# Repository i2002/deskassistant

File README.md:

# Deskassistant

## Introduction
Deskassistant is a compact device designed to help you increase your productivity. Placed on your desk, it keeps track of your priorities for the day and the time spent for each one. This project was presented as my graduation thesis for Computer Engineering Bachelor's Degree at Faculty of Mathematics and Computer Science, University of Bucharest.

## Repository structure
This repository contains the following:
- the software application written in QT
- PCB design for the connection board between Raspberry Pi Compute Module 5 and the rest of the peripherals (LCD display, touchscreen input, side buttons, brightness control, USB 2.0 interface)
- 3D design for the case backplate
- information about the OS-level configuration

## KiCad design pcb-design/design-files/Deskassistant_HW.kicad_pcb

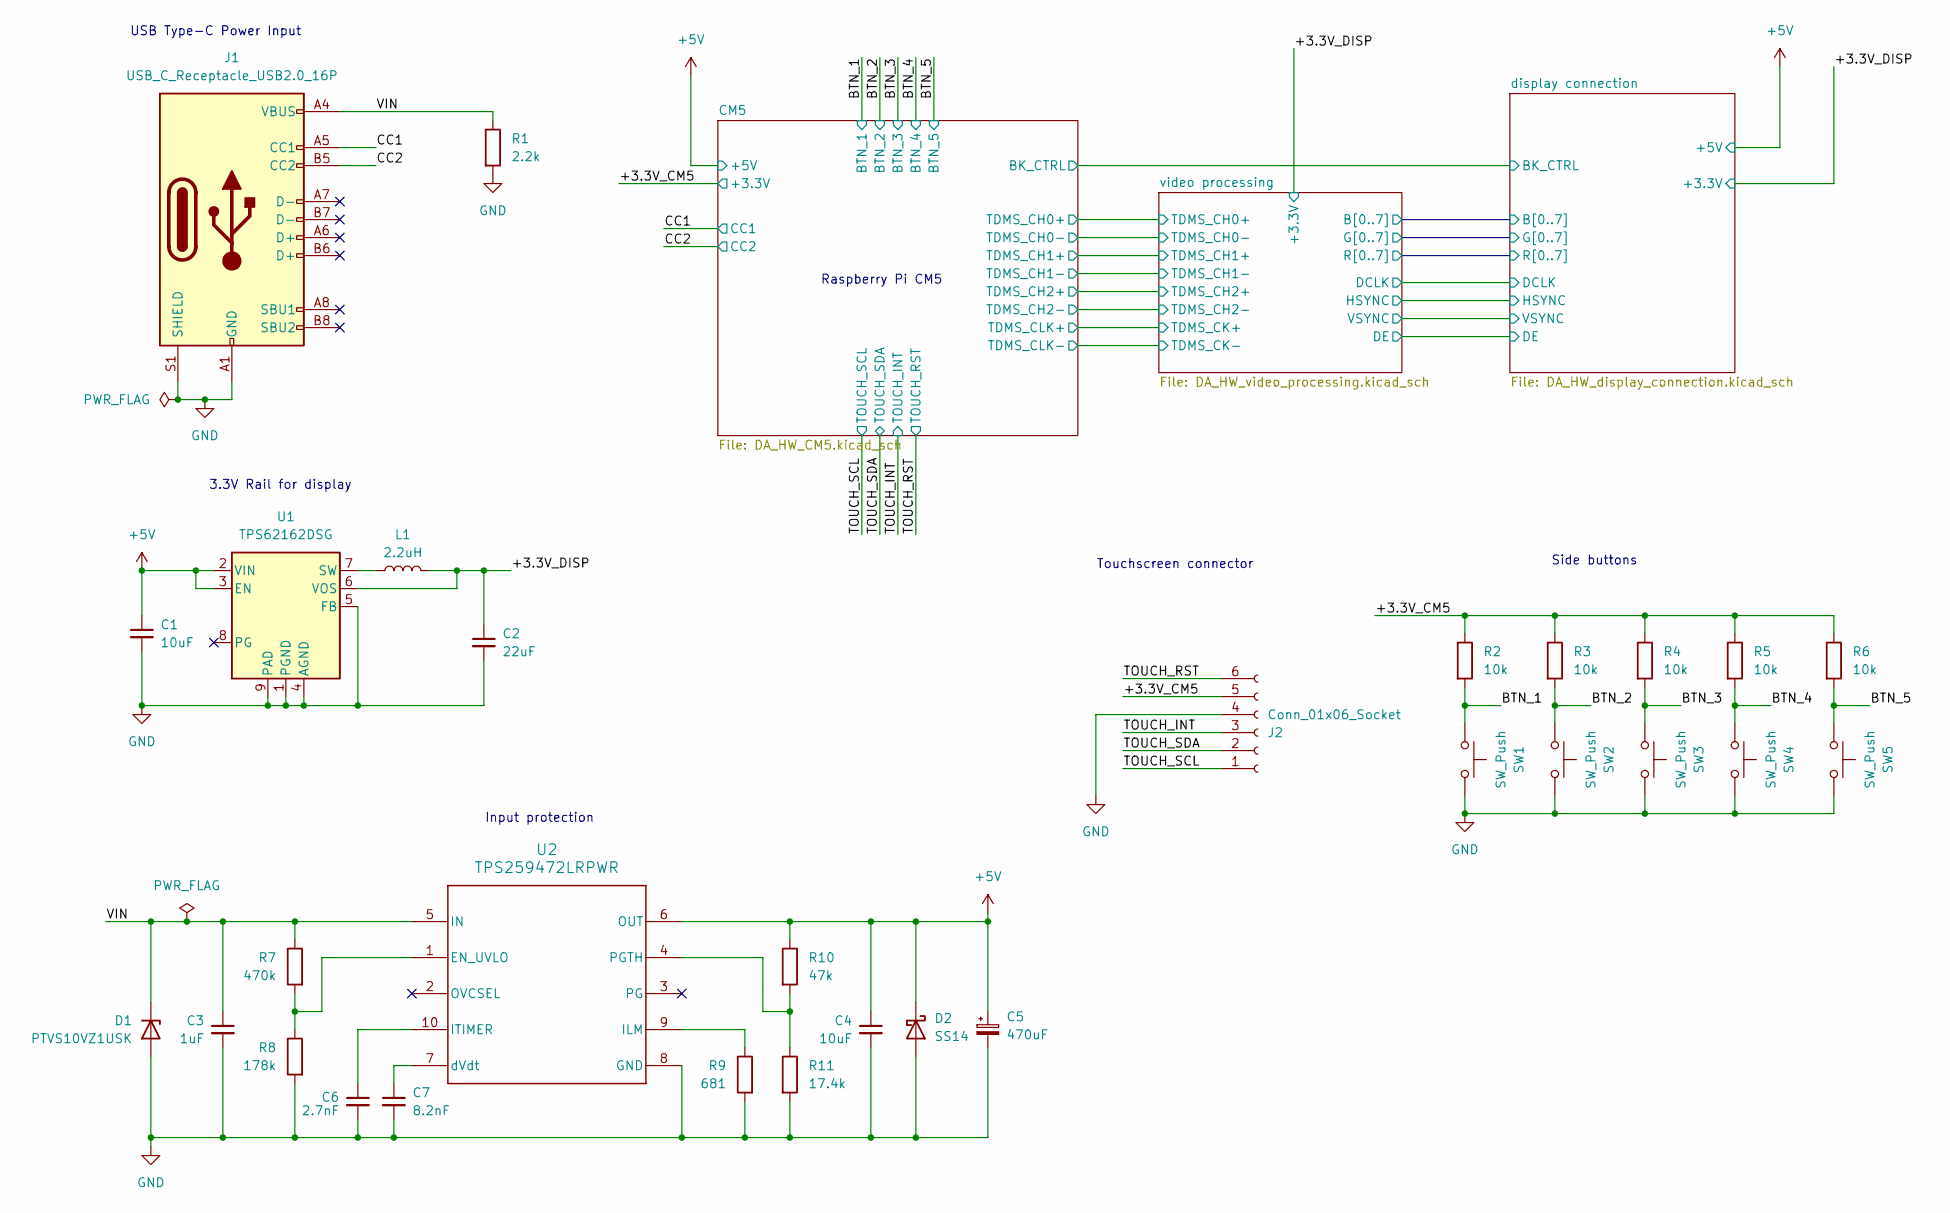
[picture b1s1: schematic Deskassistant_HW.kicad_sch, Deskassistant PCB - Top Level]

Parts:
C1, C4: 10uF; C_0805_2012Metric
C2: 22uF; C_0805_2012Metric
C3: 1uF; C_0805_2012Metric
C5: 470uF; CAPAE1030X1050L350X90N
C6: 2.7nF; C_0805_2012Metric
C7: 8.2nF; C_0805_2012Metric
D1: PTVS10VZ1USK; DIONM510X266X229L115X145N
D2: SS14; D_SMA
J1: USB_C_Receptacle_USB2.0_16P; CONN_GCT_USB4145-03-0170-C
J2: Conn_01x06_Socket; MOLEX_0527460671
L1: 2.2uH; L_NR3015T2R2M
R1: 2.2k; R_0805_2012Metric
R2, R3, R4, R5, R6: 10k; R_0805_2012Metric
R7: 470k; R_0805_2012Metric
R8: 178k; R_0805_2012Metric
R9: 681; R_0805_2012Metric
R10: 47k; R_0805_2012Metric
R11: 17.4k; R_0805_2012Metric
SW1, SW2, SW3, SW4, SW5: SW_Push; SW_ESWITCH_TL3330AF260QG
U1: TPS62162DSG; SON50P200X200X80-9N
U2: TPS259472LRPWR; ICS_TI_TPS259472ARPWR

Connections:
+5V: C1.1, C4.1, C5.1, D2.1 (K), R10.1, U1.2 (VIN), U1.3 (EN), U2.6 (OUT); also elsewhere on the board
/+3.3V_CM5: J2.5, R2.1, R3.1, R4.1, R5.1, R6.1; also elsewhere on the board
/+3.3V_DISP: C2.1, L1.2, U1.6 (VOS); also elsewhere on the board
/BTN_1: R2.2, SW1.1; also elsewhere on the board
/BTN_2: R3.2, SW2.1; also elsewhere on the board
/BTN_3: R4.2, SW3.1; also elsewhere on the board
/BTN_4: R5.2, SW4.1; also elsewhere on the board
/BTN_5: R6.2, SW5.1; also elsewhere on the board
/CC1: J1.A5 (CC1); also elsewhere on the board
/CC2: J1.B5 (CC2); also elsewhere on the board
/TOUCH_INT: J2.3; also elsewhere on the board
/TOUCH_RST: J2.6; also elsewhere on the board
/TOUCH_SCL: J2.1; also elsewhere on the board
/TOUCH_SDA: J2.2; also elsewhere on the board
/VIN: C3.1, D1.1 (K), J1.A4 (VBUS), J1.A9 (VBUS), J1.B4 (VBUS), J1.B9 (VBUS), R1.1, R7.1, U2.5 (IN)
GND: C1.2, C2.2, C3.2, C4.2, C5.2, C6.2, C7.2, D1.2 (A), D2.2 (A), J1.A1 (GND), J1.A12 (GND), J1.B1 (GND), J1.B12 (GND), J1.S1 (SHIELD), J2.4, J2.7, R1.2, R8.2, R9.2, R11.2, SW1.2, SW2.2, SW3.2, SW4.2, SW5.2, U1.1 (PGND), U1.4 (AGND), U1.5 (FB), U1.9 (PAD), U1.10, U1.11, U2.8 (GND); also elsewhere on the board
unnamed: L1.1, U1.7 (SW)
unnamed: R7.2, R8.1, U2.1 (EN_UVLO)
unnamed: R9.1, U2.9 (ILM)
unnamed: C6.1, U2.10 (ITIMER)
unnamed: R10.2, R11.1, U2.4 (PGTH)
unnamed: C7.1, U2.7 (dVdt)

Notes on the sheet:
3.3V Rail for display
USB Type-C Power Input
Input protection
Touchscreen connector
Side buttons
Raspberry Pi CM5

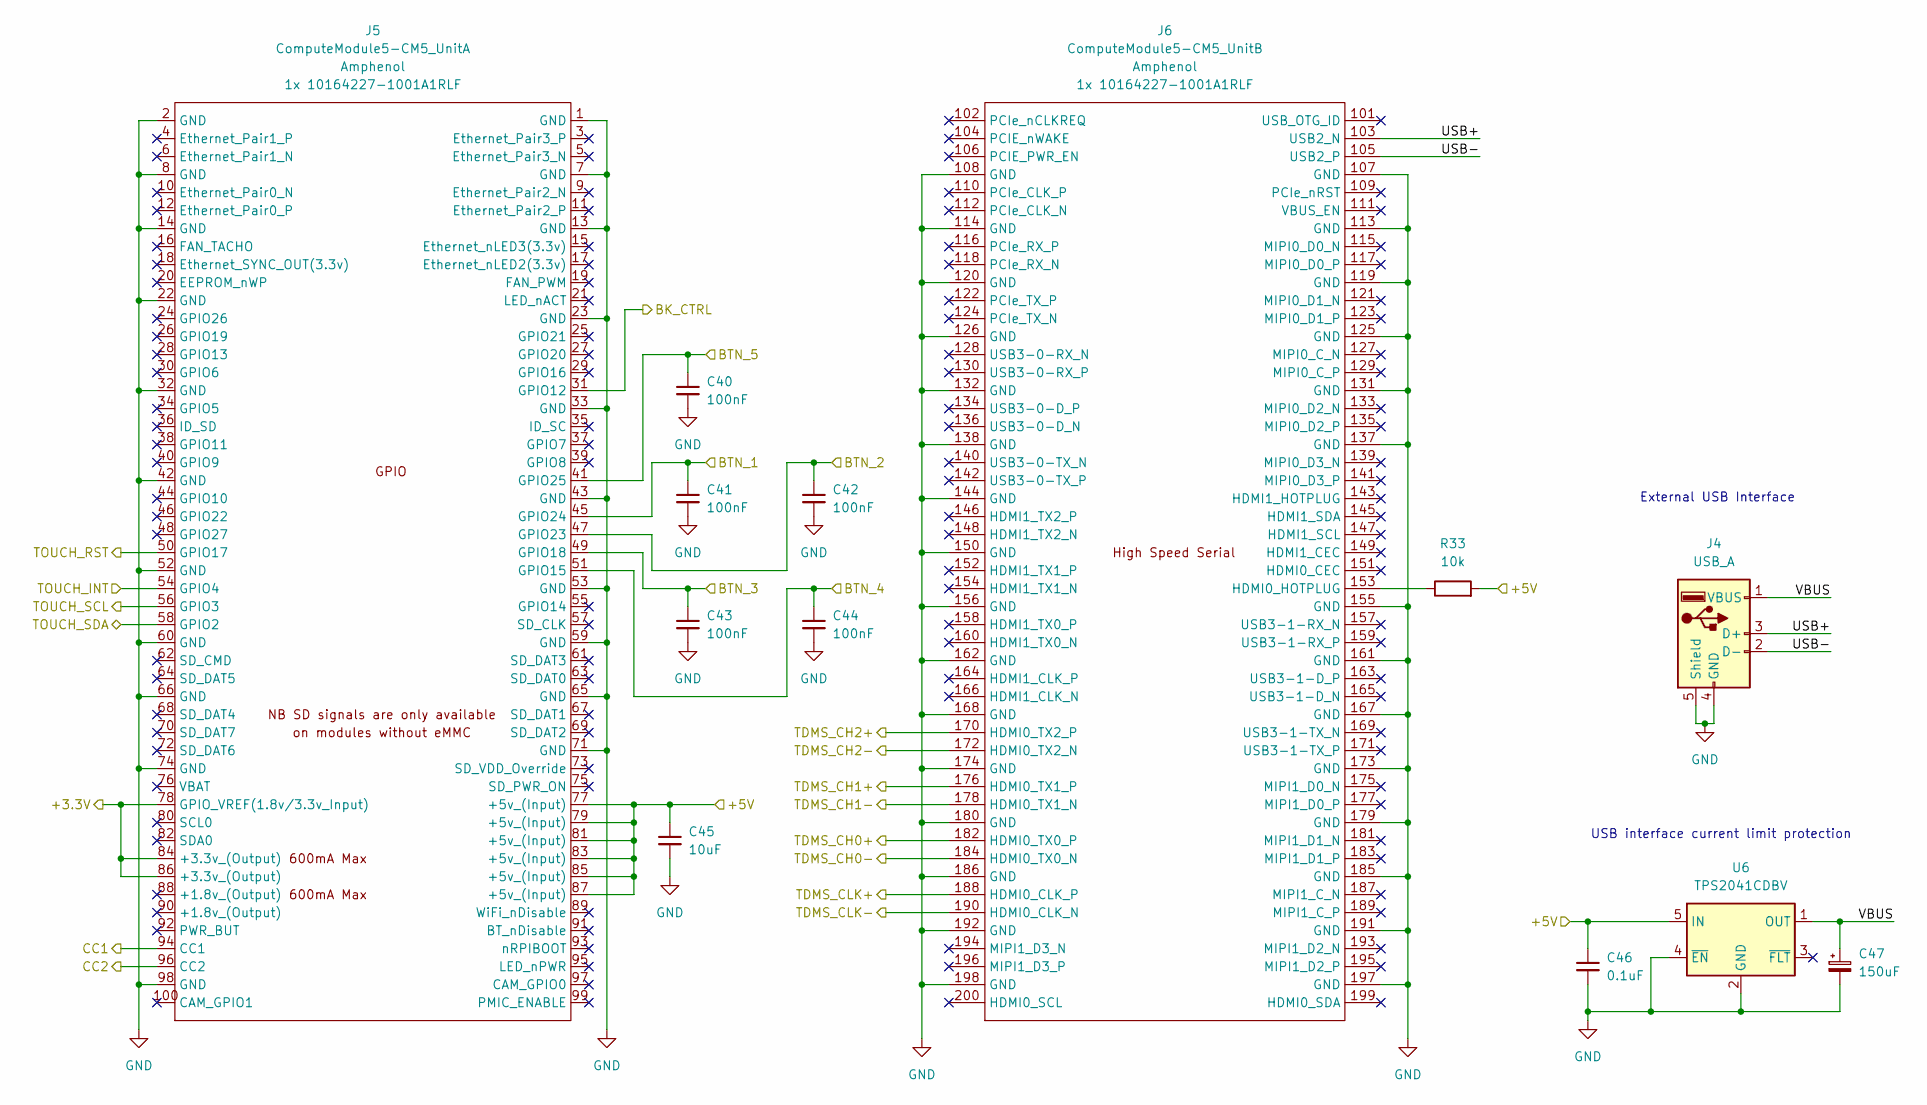
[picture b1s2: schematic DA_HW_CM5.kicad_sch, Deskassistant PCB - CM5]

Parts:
C40, C41, C42, C43, C44: 100nF; C_0805_2012Metric
C45: 10uF; C_0805_2012Metric
C46: 0.1uF; C_0805_2012Metric
C47: 150uF; CAPPM730X435X310L135X240NN
J4: USB_A; AMPHENOL_UE27AE54100
J5: ComputeModule5-CM5_UnitA; CONN_AMPHENOL_10164227-1001A1RLF_UnitA
J6: ComputeModule5-CM5_UnitB; CONN_AMPHENOL_10164227-1001A1RLF_UnitB
R33: 10k; R_0805_2012Metric
U6: TPS2041CDBV; SOT-23-5

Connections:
+5V: C45.1, C46.1, J5.77 (+5v_(Input)), J5.79 (+5v_(Input)), J5.81 (+5v_(Input)), J5.83 (+5v_(Input)), J5.85 (+5v_(Input)), J5.87 (+5v_(Input)), R33.2, U6.5 (IN); also elsewhere on the board
/+3.3V_CM5: J5.78 (GPIO_VREF(1.8v/3.3v_Input)), J5.84 (+3.3v_(Output)), J5.86 (+3.3v_(Output)); also elsewhere on the board
/BTN_1: C41.1, J5.45 (GPIO24); also elsewhere on the board
/BTN_2: C42.1, J5.47 (GPIO23); also elsewhere on the board
/BTN_3: C43.1, J5.49 (GPIO18); also elsewhere on the board
/BTN_4: C44.1, J5.51 (GPIO15); also elsewhere on the board
/BTN_5: C40.1, J5.41 (GPIO25); also elsewhere on the board
/CC1: J5.94 (CC1); also elsewhere on the board
/CC2: J5.96 (CC2); also elsewhere on the board
/CM5/BK_CTRL: J5.31 (GPIO12); also elsewhere on the board
/CM5/TDMS_CH0+: J6.182 (HDMI0_TX0_P); also elsewhere on the board
/CM5/TDMS_CH0-: J6.184 (HDMI0_TX0_N); also elsewhere on the board
/CM5/TDMS_CH1+: J6.176 (HDMI0_TX1_P); also elsewhere on the board
/CM5/TDMS_CH1-: J6.178 (HDMI0_TX1_N); also elsewhere on the board
/CM5/TDMS_CH2+: J6.170 (HDMI0_TX2_P); also elsewhere on the board
/CM5/TDMS_CH2-: J6.172 (HDMI0_TX2_N); also elsewhere on the board
/CM5/TDMS_CLK+: J6.188 (HDMI0_CLK_P); also elsewhere on the board
/CM5/TDMS_CLK-: J6.190 (HDMI0_CLK_N); also elsewhere on the board
/CM5/VBUS: C47.1, J4.1 (VBUS), U6.1 (OUT)
/TOUCH_INT: J5.54 (GPIO4); also elsewhere on the board
/TOUCH_RST: J5.50 (GPIO17); also elsewhere on the board
/TOUCH_SCL: J5.56 (GPIO3); also elsewhere on the board
/TOUCH_SDA: J5.58 (GPIO2); also elsewhere on the board
GND: C40.2, C41.2, C42.2, C43.2, C44.2, C45.2, C46.2, C47.2, J4.4 (GND), J4.5 (Shield), J5.1 (GND), J5.2 (GND), J5.7 (GND), J5.8 (GND), J5.13 (GND), J5.14 (GND), J5.22 (GND), J5.23 (GND), J5.32 (GND), J5.33 (GND), J5.42 (GND), J5.43 (GND), J5.52 (GND), J5.53 (GND), J5.59 (GND), J5.60 (GND), J5.65 (GND), J5.66 (GND), J5.71 (GND), J5.74 (GND), J5.98 (GND), J6.107 (GND), J6.108 (GND), J6.113 (GND), J6.114 (GND), J6.119 (GND), J6.120 (GND), J6.125 (GND), J6.126 (GND), J6.131 (GND), J6.132 (GND), J6.137 (GND), J6.138 (GND), J6.144 (GND), J6.150 (GND), J6.155 (GND), J6.156 (GND), J6.161 (GND), J6.162 (GND), J6.167 (GND), J6.168 (GND), J6.173 (GND), J6.174 (GND), J6.179 (GND), J6.180 (GND), J6.185 (GND), J6.186 (GND), J6.191 (GND), J6.192 (GND), J6.197 (GND), J6.198 (GND), U6.2 (GND), U6.4 (~EN); also elsewhere on the board
unnamed: J6.153 (HDMI0_HOTPLUG), R33.1

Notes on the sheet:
USB interface current limit protection
External USB Interface

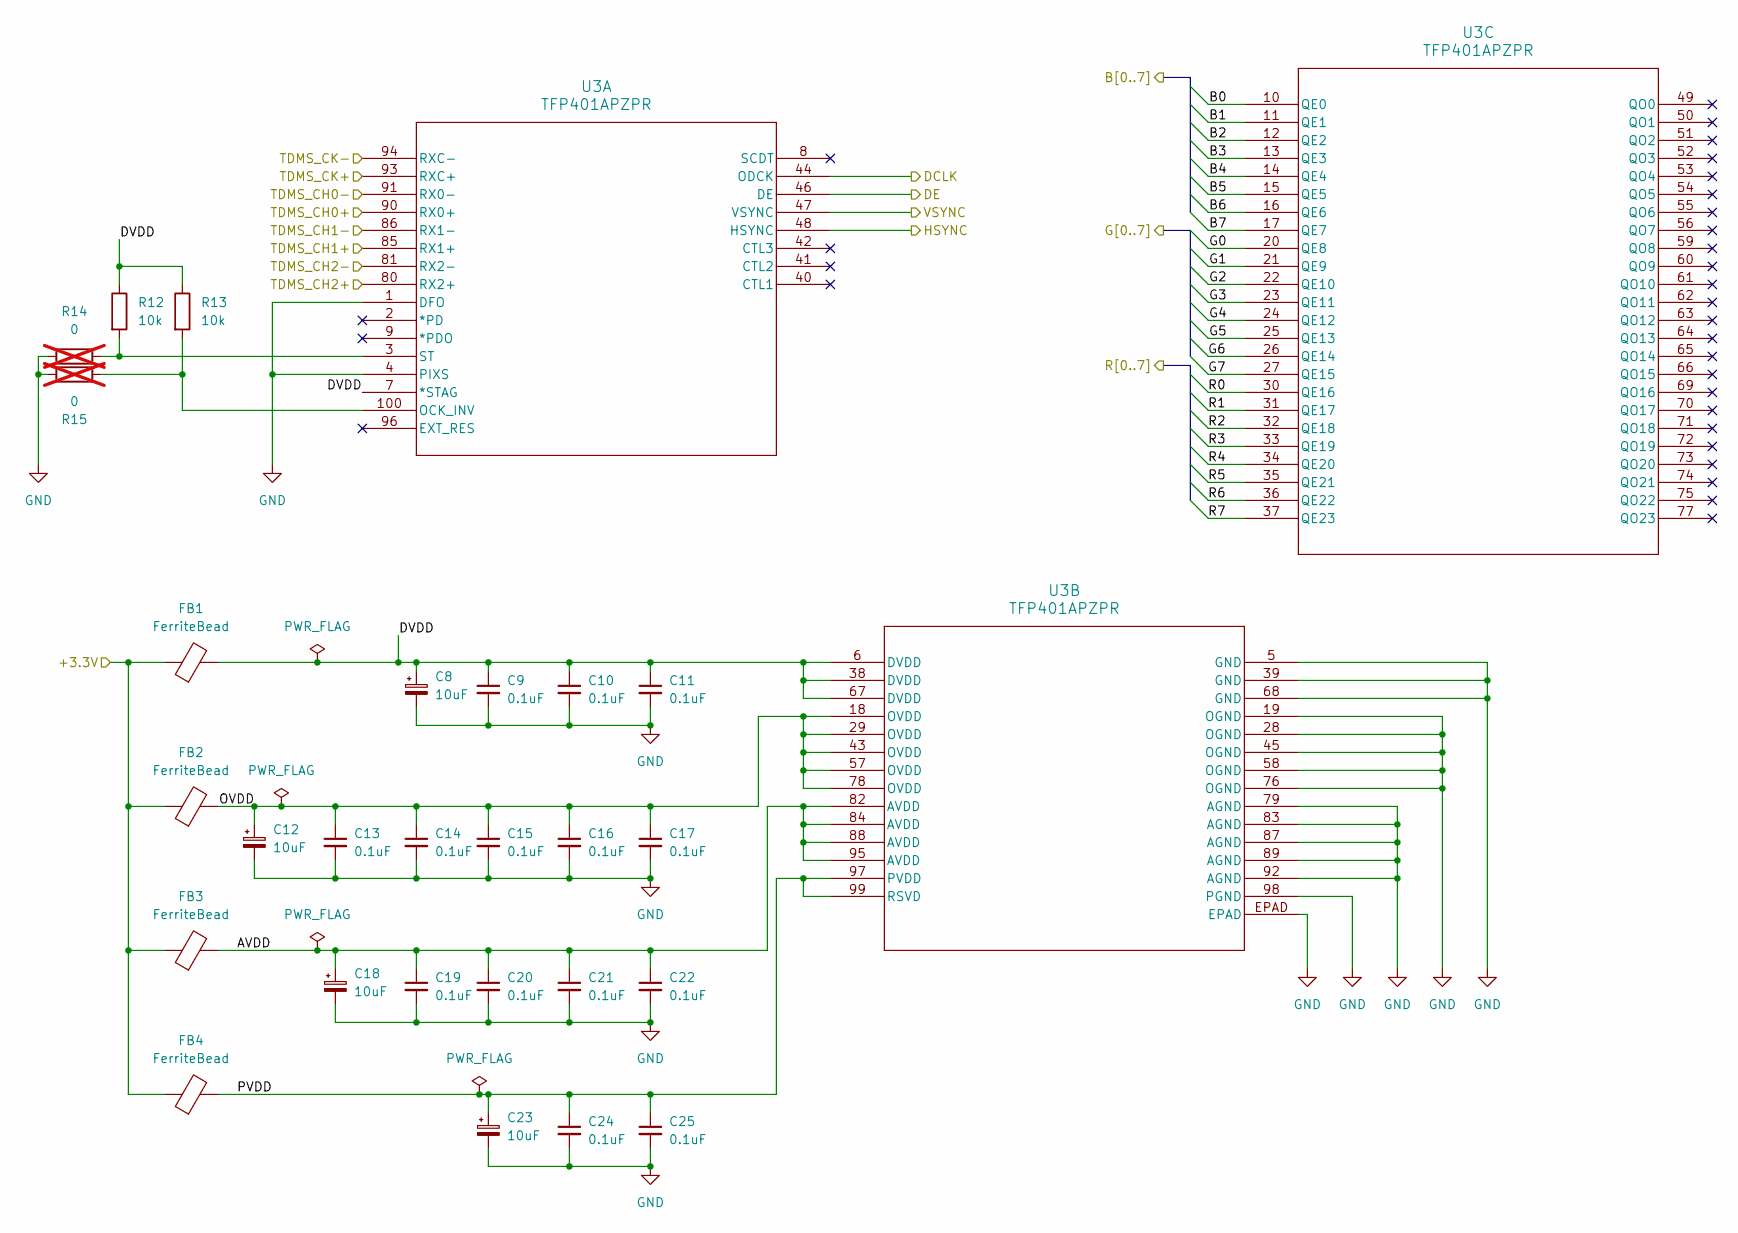
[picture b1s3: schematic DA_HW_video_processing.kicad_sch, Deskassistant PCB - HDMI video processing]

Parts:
C8, C12, C18, C23: 10uF; C_1210_3225Metric
C9, C10, C11, C13, C14, C15, C16, C17, C19, C20, C21, C22, C24, C25: 0.1uF; C_0805_2012Metric
FB1, FB2, FB3, FB4: FerriteBead; L_0603_1608Metric
R12, R13: 10k; R_0805_2012Metric
R14, R15: 0; R_0805_2012Metric; not fitted
U3: TFP401APZPR; PZP100_5P2X5P2

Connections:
/+3.3V_DISP: FB1.1, FB2.1, FB3.1, FB4.1; also elsewhere on the board
/CM5/TDMS_CH0+: U3.90 (RX0+); also elsewhere on the board
/CM5/TDMS_CH0-: U3.91 (RX0-); also elsewhere on the board
/CM5/TDMS_CH1+: U3.85 (RX1+); also elsewhere on the board
/CM5/TDMS_CH1-: U3.86 (RX1-); also elsewhere on the board
/CM5/TDMS_CH2+: U3.80 (RX2+); also elsewhere on the board
/CM5/TDMS_CH2-: U3.81 (RX2-); also elsewhere on the board
/CM5/TDMS_CLK+: U3.93 (RXC+); also elsewhere on the board
/CM5/TDMS_CLK-: U3.94 (RXC-); also elsewhere on the board
/display connection/B0: U3.10 (QE0); also elsewhere on the board
/display connection/B1: U3.11 (QE1); also elsewhere on the board
/display connection/B2: U3.12 (QE2); also elsewhere on the board
/display connection/B3: U3.13 (QE3); also elsewhere on the board
/display connection/B4: U3.14 (QE4); also elsewhere on the board
/display connection/B5: U3.15 (QE5); also elsewhere on the board
/display connection/B6: U3.16 (QE6); also elsewhere on the board
/display connection/B7: U3.17 (QE7); also elsewhere on the board
/display connection/DCLK: U3.44 (ODCK); also elsewhere on the board
/display connection/DE: U3.46 (DE); also elsewhere on the board
/display connection/G0: U3.20 (QE8); also elsewhere on the board
/display connection/G1: U3.21 (QE9); also elsewhere on the board
/display connection/G2: U3.22 (QE10); also elsewhere on the board
/display connection/G3: U3.23 (QE11); also elsewhere on the board
/display connection/G4: U3.24 (QE12); also elsewhere on the board
/display connection/G5: U3.25 (QE13); also elsewhere on the board
/display connection/G6: U3.26 (QE14); also elsewhere on the board
/display connection/G7: U3.27 (QE15); also elsewhere on the board
/display connection/HSYNC: U3.48 (HSYNC); also elsewhere on the board
/display connection/R0: U3.30 (QE16); also elsewhere on the board
/display connection/R1: U3.31 (QE17); also elsewhere on the board
/display connection/R2: U3.32 (QE18); also elsewhere on the board
/display connection/R3: U3.33 (QE19); also elsewhere on the board
/display connection/R4: U3.34 (QE20); also elsewhere on the board
/display connection/R5: U3.35 (QE21); also elsewhere on the board
/display connection/R6: U3.36 (QE22); also elsewhere on the board
/display connection/R7: U3.37 (QE23); also elsewhere on the board
/display connection/VSYNC: U3.47 (VSYNC); also elsewhere on the board
/video processing/AVDD: C18.1, C19.1, C20.1, C21.1, C22.1, FB3.2, U3.82 (AVDD), U3.84 (AVDD), U3.88 (AVDD), U3.95 (AVDD)
/video processing/DVDD: C8.1, C9.1, C10.1, C11.1, FB1.2, R12.1, R13.1, U3.6 (DVDD), U3.7 (*STAG), U3.38 (DVDD), U3.67 (DVDD)
/video processing/OVDD: C12.1, C13.1, C14.1, C15.1, C16.1, C17.1, FB2.2, U3.18 (OVDD), U3.29 (OVDD), U3.43 (OVDD), U3.57 (OVDD), U3.78 (OVDD)
/video processing/PVDD: C23.1, C24.1, C25.1, FB4.2, U3.97 (PVDD), U3.99 (RSVD)
GND: C8.2, C9.2, C10.2, C11.2, C12.2, C13.2, C14.2, C15.2, C16.2, C17.2, C18.2, C19.2, C20.2, C21.2, C22.2, C23.2, C24.2, C25.2, R14.1, R15.1, U3.1 (DFO), U3.4 (PIXS), U3.5 (GND), U3.19 (OGND), U3.28 (OGND), U3.39 (GND), U3.45 (OGND), U3.58 (OGND), U3.68 (GND), U3.76 (OGND), U3.79 (AGND), U3.83 (AGND), U3.87 (AGND), U3.89 (AGND), U3.92 (AGND), U3.98 (PGND), U3.101, U3.EPAD, U3.V (Pad); also elsewhere on the board
unnamed: R13.2, R15.2, U3.100 (OCK_INV)
unnamed: R12.2, R14.2, U3.3 (ST)

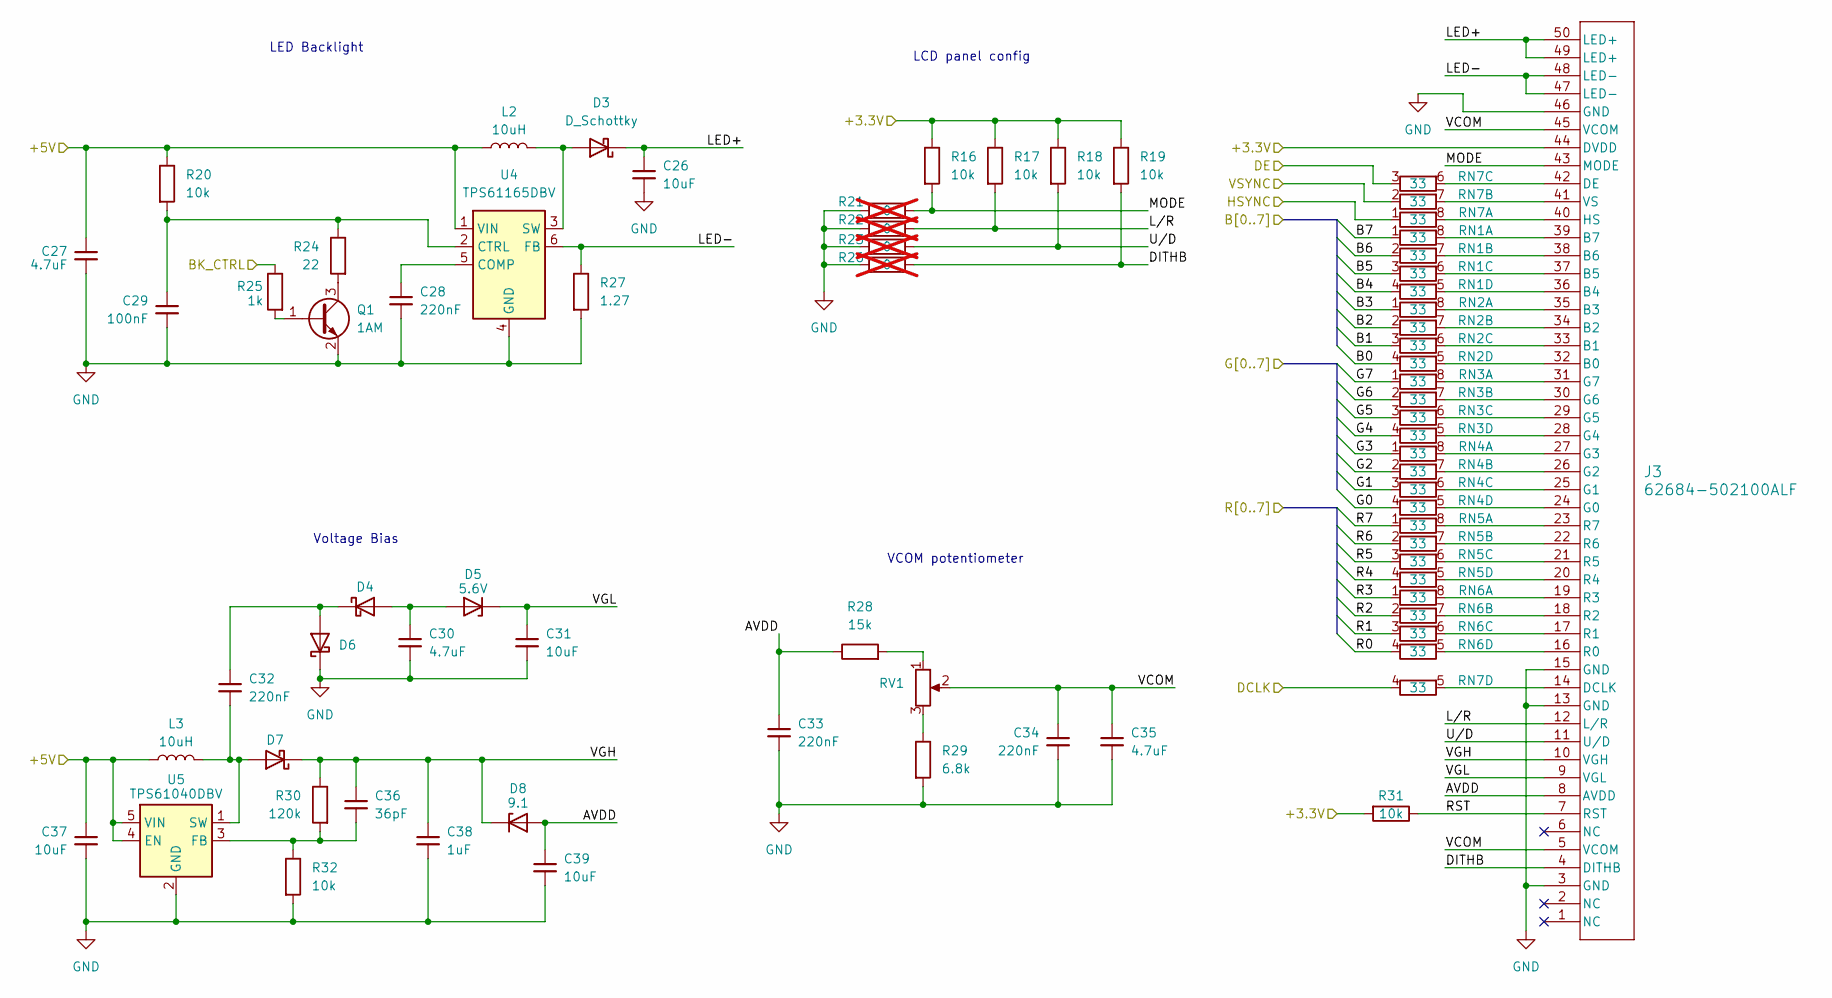
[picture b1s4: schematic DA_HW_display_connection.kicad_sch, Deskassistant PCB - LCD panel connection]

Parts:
C26, C31, C37, C39: 10uF; C_0805_2012Metric
C27, C30, C35: 4.7uF; C_0805_2012Metric
C28, C32, C33, C34: 220nF; C_0805_2012Metric
C29: 100nF; C_0805_2012Metric
C36: 36pF; C_0805_2012Metric
C38: 1uF; C_0805_2012Metric
D3, D4, D6, D7: D_Schottky; D_SMA
D5: 5.6V; D_SOD-123
D8: 9.1; D_SOD-123
J3: 62684-502100ALF; CONN50_62684-502100ALF_FCI
L2, L3: 10uH; L_Sumida_CR75
Q1: 1AM; NXP_BC847A_215
R16, R17, R18, R19, R20, R31, R32: 10k; R_0805_2012Metric
R21, R22, R23, R26: 0; R_0805_2012Metric; not fitted
R24: 22; R_0805_2012Metric
R25: 1k; R_0805_2012Metric
R27: 1.27; R_0805_2012Metric
R28: 15k; R_0805_2012Metric
R29: 6.8k; R_0805_2012Metric
R30: 120k; R_0805_2012Metric
RN1, RN2, RN3, RN4, RN5, RN6, RN7: 33; R_Array_Convex_4x0603
RV1: Potentiometer_Bourns_3214J_Horizontal
U4: TPS61165DBV; SOT-23-6
U5: TPS61040DBV; SOT-23-5

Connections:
+5V: C27.1, C37.1, L2.1, L3.1, R20.1, U4.1 (VIN), U5.4 (EN), U5.5 (VIN); also elsewhere on the board
/+3.3V_DISP: J3.44 (DVDD), R16.1, R17.1, R18.1, R19.1, R31.2; also elsewhere on the board
/CM5/BK_CTRL: R25.1; also elsewhere on the board
/display connection/AVDD: C33.1, C39.1, D8.2 (A), J3.8 (AVDD), R28.1
/display connection/B0: RN2.4 (R4.1); also elsewhere on the board
/display connection/B1: RN2.3 (R3.1); also elsewhere on the board
/display connection/B2: RN2.2 (R2.1); also elsewhere on the board
/display connection/B3: RN2.1 (R1.1); also elsewhere on the board
/display connection/B4: RN1.4 (R4.1); also elsewhere on the board
/display connection/B5: RN1.3 (R3.1); also elsewhere on the board
/display connection/B6: RN1.2 (R2.1); also elsewhere on the board
/display connection/B7: RN1.1 (R1.1); also elsewhere on the board
/display connection/DCLK: RN7.4 (R4.1); also elsewhere on the board
/display connection/DE: RN7.3 (R3.1); also elsewhere on the board
/display connection/DITHB: J3.4 (DITHB), R19.2, R26.2
/display connection/G0: RN4.4 (R4.1); also elsewhere on the board
/display connection/G1: RN4.3 (R3.1); also elsewhere on the board
/display connection/G2: RN4.2 (R2.1); also elsewhere on the board
/display connection/G3: RN4.1 (R1.1); also elsewhere on the board
/display connection/G4: RN3.4 (R4.1); also elsewhere on the board
/display connection/G5: RN3.3 (R3.1); also elsewhere on the board
/display connection/G6: RN3.2 (R2.1); also elsewhere on the board
/display connection/G7: RN3.1 (R1.1); also elsewhere on the board
/display connection/HSYNC: RN7.1 (R1.1); also elsewhere on the board
/display connection/LED+: C26.1, D3.1 (K), J3.49 (LED+), J3.50 (LED+)
/display connection/LED-: J3.47 (LED-), J3.48 (LED-), R27.1, U4.6 (FB)
/display connection/L/R: J3.12 (L/R), R17.2, R22.2
/display connection/MODE: J3.43 (MODE), R16.2, R21.2
/display connection/R0: RN6.4 (R4.1); also elsewhere on the board
/display connection/R1: RN6.3 (R3.1); also elsewhere on the board
/display connection/R2: RN6.2 (R2.1); also elsewhere on the board
/display connection/R3: RN6.1 (R1.1); also elsewhere on the board
/display connection/R4: RN5.4 (R4.1); also elsewhere on the board
/display connection/R5: RN5.3 (R3.1); also elsewhere on the board
/display connection/R6: RN5.2 (R2.1); also elsewhere on the board
/display connection/R7: RN5.1 (R1.1); also elsewhere on the board
/display connection/RST: J3.7 (RST), R31.1
/display connection/U/D: J3.11 (U/D), R18.2, R23.2
/display connection/VCOM: C34.1, C35.1, J3.5 (VCOM), J3.45 (VCOM), RV1.2
/display connection/VGH: C36.1, C38.1, D7.1 (K), D8.1 (K), J3.10 (VGH), R30.1
/display connection/VGL: C31.1, D5.1 (K), J3.9 (VGL)
/display connection/VSYNC: RN7.2 (R2.1); also elsewhere on the board
GND: C26.2, C27.2, C28.2, C29.2, C30.2, C31.2, C33.2, C34.2, C35.2, C37.2, C38.2, C39.2, D6.1 (K), J3.3 (GND), J3.13 (GND), J3.15 (GND), J3.46 (GND), J3.51, Q1.2 (E), R21.1, R22.1, R23.1, R26.1, R27.2, R29.2, R32.2, U4.4 (GND), U5.2 (GND); also elsewhere on the board
unnamed: D3.2 (A), L2.2, U4.3 (SW)
unnamed: C30.1, D4.2 (A), D5.2 (A)
unnamed: C32.1, D4.1 (K), D6.2 (A)
unnamed: C32.2, D7.2 (A), L3.2, U5.1 (SW)
unnamed: J3.32 (B0), RN2.5 (R4.2)
unnamed: J3.33 (B1), RN2.6 (R3.2)
unnamed: J3.34 (B2), RN2.7 (R2.2)
unnamed: J3.35 (B3), RN2.8 (R1.2)
unnamed: J3.36 (B4), RN1.5 (R4.2)
unnamed: J3.37 (B5), RN1.6 (R3.2)
unnamed: J3.38 (B6), RN1.7 (R2.2)
unnamed: J3.39 (B7), RN1.8 (R1.2)
unnamed: J3.14 (DCLK), RN7.5 (R4.2)
unnamed: J3.42 (DE), RN7.6 (R3.2)
unnamed: J3.24 (G0), RN4.5 (R4.2)
unnamed: J3.25 (G1), RN4.6 (R3.2)
unnamed: J3.26 (G2), RN4.7 (R2.2)
unnamed: J3.27 (G3), RN4.8 (R1.2)
unnamed: J3.28 (G4), RN3.5 (R4.2)
unnamed: J3.29 (G5), RN3.6 (R3.2)
unnamed: J3.30 (G6), RN3.7 (R2.2)
unnamed: J3.31 (G7), RN3.8 (R1.2)
unnamed: J3.40 (HS), RN7.8 (R1.2)
unnamed: J3.16 (R0), RN6.5 (R4.2)
unnamed: J3.17 (R1), RN6.6 (R3.2)
unnamed: J3.18 (R2), RN6.7 (R2.2)
unnamed: J3.19 (R3), RN6.8 (R1.2)
unnamed: J3.20 (R4), RN5.5 (R4.2)
unnamed: J3.21 (R5), RN5.6 (R3.2)
unnamed: J3.22 (R6), RN5.7 (R2.2)
unnamed: J3.23 (R7), RN5.8 (R1.2)
unnamed: J3.41 (VS), RN7.7 (R2.2)
unnamed: Q1.1 (B), R25.2
unnamed: Q1.3 (C), R24.2
unnamed: R28.2, RV1.1
unnamed: R29.1, RV1.3
unnamed: C28.1, U4.5 (COMP)
unnamed: C29.1, R20.2, R24.1, U4.2 (CTRL)
unnamed: C36.2, R30.2, R32.1, U5.3 (FB)

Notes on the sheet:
VCOM potentiometer
LCD panel config
LED Backlight
Voltage Bias

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
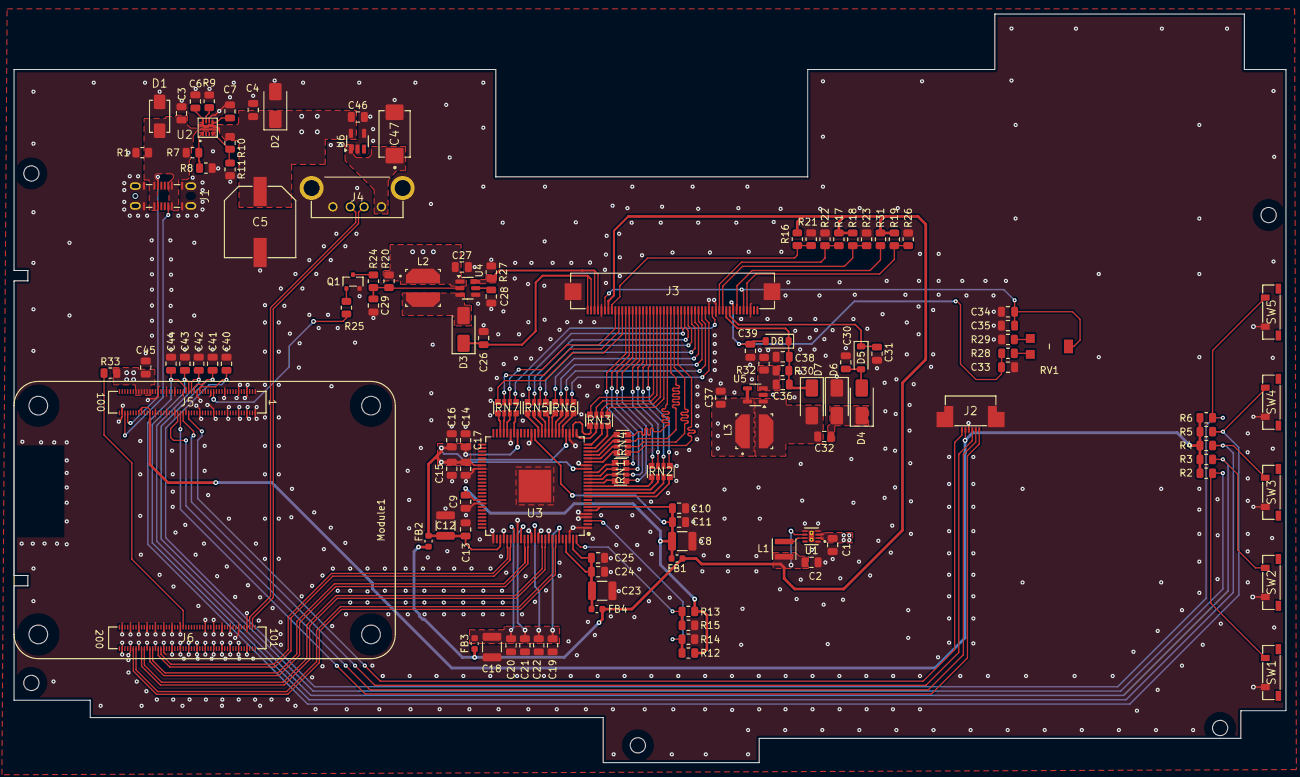
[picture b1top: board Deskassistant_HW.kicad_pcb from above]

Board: 4 copper layers, 183.5 x 108.0 mm, 122 parts (0 on the bottom side), 119 nets.

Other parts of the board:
Module1: ComputeModule5-CM5; Raspberry-Pi-5-Compute-Module

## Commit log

2025-06-29 Initial public commit for HW data
2025-06-30 Update pcb schematic output pdf
2025-08-25 Fix HW rev B issues
2025-08-25 Add unit of measure to D8 value
2025-09-01 Fix USB D+ and D- connections
